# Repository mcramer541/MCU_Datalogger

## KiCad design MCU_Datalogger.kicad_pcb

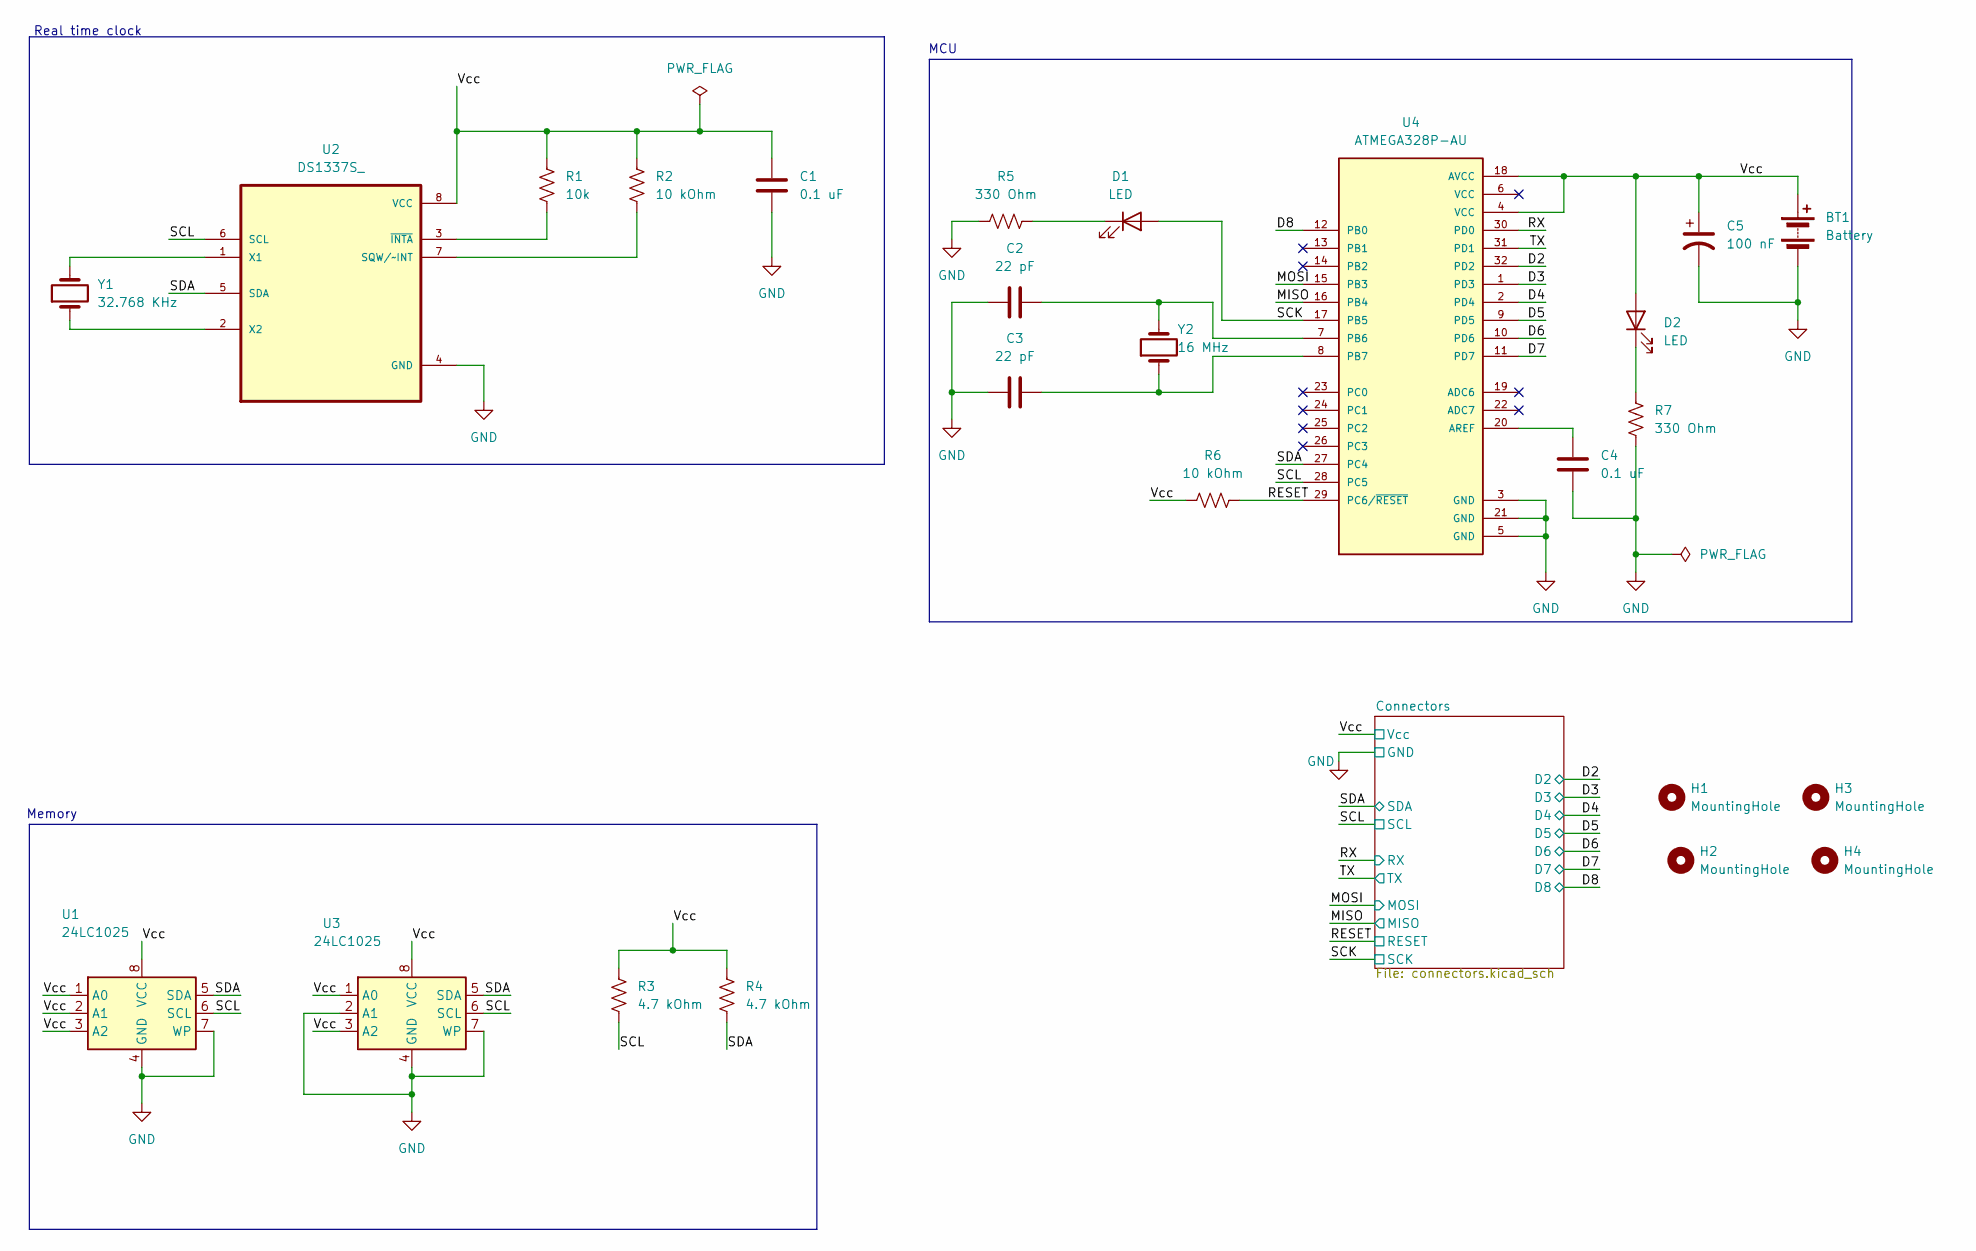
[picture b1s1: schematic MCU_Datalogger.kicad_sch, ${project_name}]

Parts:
BT1: Battery; PinHeader_1x02_P2.54mm_Vertical
C1, C4: 0.1 uF; C_0805_2012Metric
C2, C3: 22 pF; C_0805_2012Metric
C5: 100 nF; C_0805_2012Metric
D1, D2: LED; LED_0805_2012Metric
H1, H2, H3, H4: MountingHole; MountingHole_2.1mm
R1: 10k; R_0805_2012Metric
R2, R6: 10 kOhm; R_0805_2012Metric
R3, R4: 4.7 kOhm; R_0805_2012Metric
R5, R7: 330 Ohm; R_0805_2012Metric
U1, U3: 24LC1025; SOIC-8_5.3x5.3mm_P1.27mm
U2: DS1337S_; SOIC127P600X175-8N
U4: ATMEGA328P-AU; QFP80P900X900X120-32N; PARTREV 8271A
Y1: 32.768 KHz; Crystal_SMD_5032-2Pin_5.0x3.2mm_HandSoldering
Y2: 16 MHz; Crystal_SMD_5032-2Pin_5.0x3.2mm_HandSoldering

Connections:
/D2: U4.32 (PD2); also elsewhere on the board
/D3: U4.1 (PD3); also elsewhere on the board
/D4: U4.2 (PD4); also elsewhere on the board
/D5: U4.9 (PD5); also elsewhere on the board
/D6: U4.10 (PD6); also elsewhere on the board
/D7: U4.11 (PD7); also elsewhere on the board
/D8: U4.12 (PB0); also elsewhere on the board
/MISO: U4.16 (PB4); also elsewhere on the board
/MOSI: U4.15 (PB3); also elsewhere on the board
/RESET: R6.2, U4.29 (PC6/~RESET); also elsewhere on the board
/RX: U4.30 (PD0); also elsewhere on the board
/SCK: D1.2 (A), U4.17 (PB5); also elsewhere on the board
/SCL: R3.2, U1.6 (SCL), U2.6 (SCL), U3.6 (SCL), U4.28 (PC5); also elsewhere on the board
/SDA: R4.2, U1.5 (SDA), U2.5 (SDA), U3.5 (SDA), U4.27 (PC4); also elsewhere on the board
/TX: U4.31 (PD1); also elsewhere on the board
/Vcc: BT1.1 (+), C1.1, C5.1, D2.2 (A), R1.1, R2.1, R3.1, R4.1, R6.1, U1.1 (A0), U1.2 (A1), U1.3 (A2), U1.8 (VCC), U2.8 (VCC), U3.1 (A0), U3.3 (A2), U3.8 (VCC), U4.4 (VCC), U4.18 (AVCC); also elsewhere on the board
GND: BT1.2 (-), C1.2, C2.1, C3.1, C4.1, C5.2, R5.1, R7.2, U1.4 (GND), U1.7 (WP), U2.4 (GND), U3.2 (A1), U3.4 (GND), U3.7 (WP), U4.3 (GND), U4.5 (GND), U4.21 (GND); also elsewhere on the board
unnamed: D1.1 (K), R5.2
unnamed: D2.1 (K), R7.1
unnamed: R2.2, U2.7 (SQW/~INT)
unnamed: U2.1 (X1), Y1.2
unnamed: U2.2 (X2), Y1.1
unnamed: R1.2, U2.3 (~INTA)
unnamed: C4.2, U4.20 (AREF)
unnamed: C2.2, U4.7 (PB6), Y2.2
unnamed: C3.2, U4.8 (PB7), Y2.1

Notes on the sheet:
Memory
Real time clock
MCU

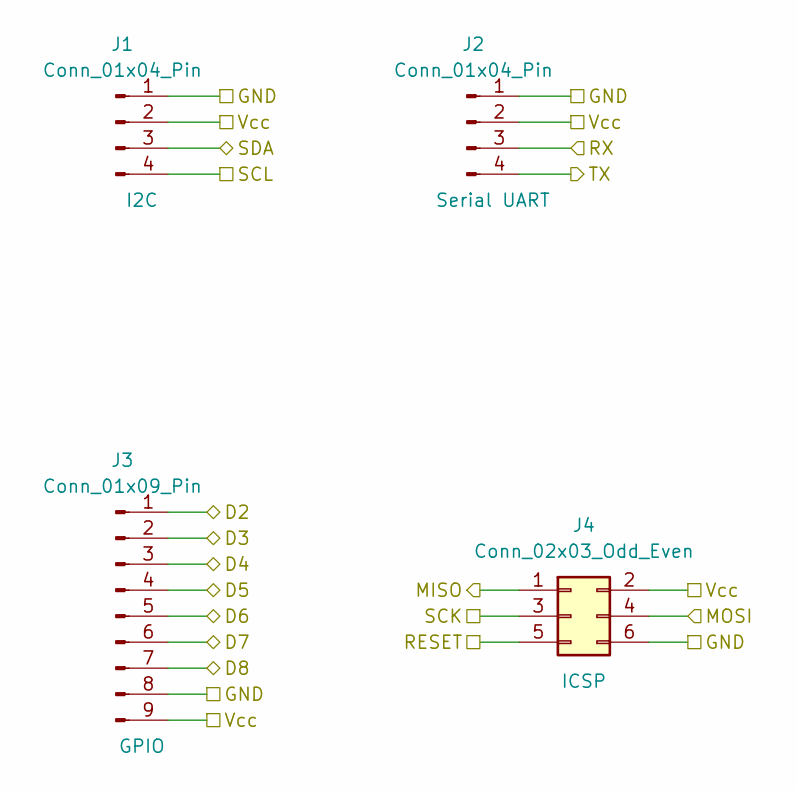
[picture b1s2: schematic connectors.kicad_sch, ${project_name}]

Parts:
J1, J2: Conn_01x04_Pin; PinHeader_1x04_P2.54mm_Vertical
J3: Conn_01x09_Pin; PinHeader_1x09_P2.54mm_Vertical
J4: Conn_02x03_Odd_Even; PinHeader_2x03_P2.54mm_Vertical

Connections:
/D2: J3.1; also elsewhere on the board
/D3: J3.2; also elsewhere on the board
/D4: J3.3; also elsewhere on the board
/D5: J3.4; also elsewhere on the board
/D6: J3.5; also elsewhere on the board
/D7: J3.6; also elsewhere on the board
/D8: J3.7; also elsewhere on the board
/MISO: J4.1; also elsewhere on the board
/MOSI: J4.4; also elsewhere on the board
/RESET: J4.5; also elsewhere on the board
/RX: J2.3; also elsewhere on the board
/SCK: J4.3; also elsewhere on the board
/SCL: J1.4; also elsewhere on the board
/SDA: J1.3; also elsewhere on the board
/TX: J2.4; also elsewhere on the board
/Vcc: J1.2, J2.2, J3.9, J4.2; also elsewhere on the board
GND: J1.1, J2.1, J3.8, J4.6; also elsewhere on the board

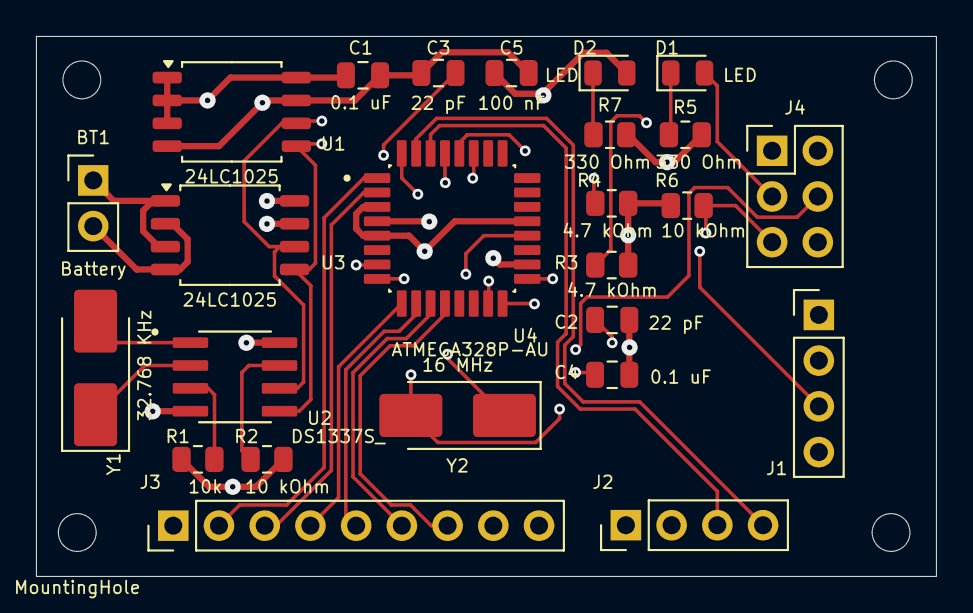
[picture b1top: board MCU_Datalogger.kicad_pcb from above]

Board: 4 copper layers, 50.0 x 30.0 mm, 29 parts (0 on the bottom side), 26 nets.

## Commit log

2025-07-08 This is the initial setup for the project
2025-07-08 test
2025-07-09 removing files that are uneeded and updating schematic settings
2025-07-09 Have added required symbols to schematic sheets
2025-07-09 Changed the location of the symbols (arrange)
2025-07-09 Upated components with values
2025-07-09 Added footprints to components in schematic and added external library for external footprints
2025-07-09 Wiring and adding netlabels to the schematic diagram for the main schematic page
2025-07-09 Completed schematic wiring and passed ERC
2025-07-09 allocated GND and Vcc nets to power net class
2025-07-14 added comments to schematic
2025-07-14 setup for the 2layer PCB schematic
2025-07-14 Placing components on the PCB
2025-07-14 routing components on PCB (still need fills for power and GND)
2025-07-14 adding fills to PCB
2025-07-14 fixed silkscreen issues
2025-07-14 fixed silkscreen issues pt2
2025-07-14 fixed issue with VCC
2025-07-14 added manufacturing information
2025-07-14 added routing for 4 layer PCB
2025-07-14 Cleanup of layout
2025-07-14 Closeout
2025-07-14 added gitattributes file for reallmao
2025-07-15 small change to schematic
2025-07-15 fixed bug that affects the clock
2025-07-15 fixed bug that affects the clock pt 2
2025-07-15 fixed pcb bug
2025-07-15 fixed git
